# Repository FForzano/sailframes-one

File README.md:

# XGSail

Open sailing analytics platform for race analysis, session replay, and fleet performance — self-hostable, hardware-agnostic, and built for extensibility.

> ☕ **[Support XGSail on Buy Me a Coffee](https://buymeacoffee.com/xgsail)** — funds
> go toward app development, publishing on the app stores (once funding allows), and
> scaling up servers as usage grows.

> **XGSail is a fork of SailFrames (originally released as "SailFrames One").**
> It keeps the original's Apache 2.0 license and general purpose — sailing
> session analytics — but is **not a drop-in copy**: the data model, API
> surface, and frontend have been substantially redesigned rather than
> incrementally patched (see "Structural differences from upstream" below).
> The name change reflects that divergence and matches the domain this fork
> is hosted under.

XGSail is a software-first evolution of the original SailFrames project. It focuses on the application layer: user management, authentication, roles, data ingestion, storage, analytics, and web-based workflows for sailors, coaches, and teams.

## What XGSail Is

XGSail is a platform for collecting, storing, and analyzing sailing session data.

It provides:

- Self-hosted deployment (Postgres + MinIO + backend + frontend + workers, one `docker compose up`)
- User authentication and role-based access (clubs, groups, boats, per-resource ownership)
- Database-backed storage for users, boats, clubs, groups, devices, sessions, races and regattas
- Session and race analysis workflows (legs, maneuvers, VMG, polar performance)
- Replay and coaching-oriented review tools (track playback, session photos)
- Hardware-agnostic ingestion through a defined protocol (`docs/device-protocol.md`) — devices claim themselves, then upload data with a per-device key
- Native iOS/Android app shells (Capacitor) around the same frontend, with self-hosted OTA JS-bundle updates (`docs/native-apps.md`, `docs/ota-updates.md`) — still frontend application + deployment configuration scope, not a hardware artifact

The goal is to provide an open platform for sailing analytics that can work with dedicated devices, custom integrations, or external data sources, without tying the application to one specific hardware stack.

## What XGSail Is Not

XGSail is **not** the hardware, firmware, or embedded edge stack from the original SailFrames repository.

Those components may integrate with XGSail through the device protocol, but this repository is focused on the software platform and its data contract.

### XGSail E1 (reference hardware)

[**xgsail-e1**](https://github.com/FForzano/xgsail-e1) is a companion
repository with the firmware and KiCad PCB design for **E1**, an
ESP32-based fleet tracker built as reference hardware for this
platform: GNSS + IMU + wind + pressure logging, an ESP-NOW peer mesh
for live fleet position sharing and on-course-side (OCS) race-start
detection, and uploads over the device protocol above — direct over
WiFi, or relayed over Bluetooth by the owner's phone when WiFi isn't
available. It's open hardware (Apache 2.0, same license as this repo)
and currently a build-it-yourself project rather than a sold product.
See that repository's `README.md` and `docs/hardware.md` for firmware,
schematics, and the BOM.

## Project Scope

This repository contains:

- Backend API (`backend/`)
- Frontend application (`frontend/`)
- Database models and Alembic migrations (`backend/db/`)
- Authentication and authorization (`backend/auth/`)
- Storage and ingestion services (`backend/storage/`, `backend/services/`)
- Processing workers (`workers/`)
- Standalone OTA update server for the native app (`ota-service/`)
- Protocol and integration documentation (`docs/`)
- Self-hosted deployment configuration (`deploy/`, `docker-compose.yml`)

## Architecture Direction

XGSail follows a software-platform approach:

1. Devices or external tools produce sailing data.
2. Data is uploaded using a stable ingestion contract.
3. The backend validates, stores, and processes session data.
4. The web application exposes analysis, replay, and management features.

This separation allows the platform to evolve independently from any one hardware implementation.

## Repository Status

XGSail is under active development. The core platform is implemented and usable end to end:

- Users, authentication, and scoped RBAC (superadmin / club admin / race officer) plus per-resource ownership for boats and groups
- Clubs, groups, boats, and devices, with a claim-flow device protocol for ingestion
- Session import and processing (legs, maneuvers, VMG, polar targets), crew tracking, and photo attachments
- Races, regattas, and race-day management, with a leaderboard
- Multi-language frontend (English/Italian) covering all of the above

Ongoing work is on usability and polish of the existing frontend, and rounding out edge cases in the ingestion and analysis pipeline — not on building the core feature set from scratch.

## Relationship to SailFrames Core

XGSail is derived from the broader SailFrames effort, but it intentionally narrows the scope to the software application layer.

Where the original project includes hardware, firmware, edge devices, and AWS-oriented infrastructure, XGSail aims to become a cleaner, self-hostable analytics platform with a stable integration surface for present and future devices.

### Structural differences from upstream

This is a fork in lineage and license, not a rebrand of the same codebase. Concretely:

- **Data model**: the users/auth/roles/clubs/groups/devices/sessions schema was redesigned from scratch, not incrementally extended from the original tables.
- **API surface**: routes, permission model, and ingestion contract were rebuilt around that new schema, including a hardware-agnostic device-claim + device-key ingestion flow (`docs/device-protocol.md`) replacing the original's device-specific upload path.
- **Frontend**: rebuilt on a simplified page structure and data-fetching approach rather than carried over as-is.
- **Scope boundary**: firmware, PCB design, and embedded-device internals are excluded entirely — they remain in the upstream hardware repository, not mirrored here even partially.

The redesign these docs specified is now implemented on `main`. The
retained docs are the source of truth going forward: `docs/device-protocol.md`
(the ingestion contract) and `docs/estimation-pipeline.md` (how raw
sensor/API data becomes legs/maneuvers/VMG/polar numbers).

## Principles

- **Open** — users can inspect, run, and extend the platform
- **Self-hostable** — no mandatory vendor lock-in
- **Hardware-agnostic** — devices integrate through protocols, not tight coupling
- **Maintainable** — clear boundaries between frontend, backend, storage, and processing
- **Extensible** — new integrations should not require rewriting the core platform

## Quick start (self-host)

Everything runs as containers. From the repo root:

```bash
docker compose up --build
```

Then open **http://localhost:8080**. That's the whole stack:

| Service | Port | What it is |
|---|---|---|
| `frontend` | 8080 | The SPA (nginx). Serves the app and proxies `/api` → backend, so it's all one origin. |
| `backend` | 8000 | The REST API (FastAPI). Also reachable directly for debugging. |
| `postgres` | 5432 | Metadata (users, boats, sessions, races, RBAC). |
| `minio` | 9000 / 9001 | S3-compatible blob storage (sensor data, video, manifests) + console. |
| `process_upload`, `video` | — | Heavy-processing workers (see below). |

No `.env` is required — every value has a dev default. Copy `.env.example` to
`.env` to override secrets for a real deployment.

## Architecture

- **One API.** The FastAPI `backend/` is the only API surface. Metadata lives in
  Postgres; large files (CSV sensor data, video, JSON results) live in S3/MinIO.
- **Auth.** Email/password (Argon2id) → short-lived JWT access token + rotating
  refresh token, per-club RBAC. Dual transport: **web** uses httpOnly cookies with
  double-submit CSRF on mutations; **native apps** get the same tokens in the
  response body and send the access token as an `Authorization: Bearer` header
  (no cookie, so CSRF doesn't apply).
- **Workers as microservices.** `workers/process_upload` (GPS tracks + analysis)
  and `workers/video` (MP4 → HLS via ffmpeg) are built on the AWS Lambda base
  image. The **same image** runs on AWS Lambda and locally: in compose it runs
  via the Lambda Runtime Interface Emulator that ships in the base image, and the
  backend invokes it over HTTP on a MinIO upload event (`/hooks/minio`). On AWS
  the identical image sits behind an S3 → Lambda trigger. No code changes to move
  between the two.

Repo layout: `backend/` · `frontend/` · `workers/{process_upload,train_maneuver,video}/` ·
`ota-service/` (standalone OTA update server) · `deploy/` (Dockerfile + MinIO init) ·
`scripts/` (migrations, backfills, calibration) · `docs/device-protocol.md`
(device integration contract) · `docs/estimation-pipeline.md` (analysis pipeline).

## Native apps (iOS/Android)

The same frontend also ships as native iOS/Android shells via
[Capacitor](https://capacitorjs.com/) — not a separate codebase, just the
existing SPA wrapped for things a browser tab can't do (background GPS
recording, Bluetooth device pairing, share-target GPX import). See
`docs/native-apps.md` for how it's built and `docs/ota-updates.md` for how
JS/CSS updates reach installs without a store release.

**Status: early, not on the official stores.**

- **Android**: buildable and signable, but not published to the Play
  Store. `.github/workflows/android-release.yml` builds a signed release
  APK on every `vX.Y.Z` tag and attaches it to the matching GitHub
  Release — install it by sideloading that APK. A `play-store-upload` job
  exists in the same workflow but is disabled.
- **iOS**: not distributable in any form yet, not even for internal
  testing — `.github/workflows/ios-release.yml` is a scaffold, disabled.

**Why not on the stores yet: cost, not effort.** Google Play requires a
one-time $25 registration fee; Apple requires a $99/year Developer
Program membership just to sign a build at all, store or not (see
"Testing without a paid Apple account" in `docs/native-apps.md`). The
plan is to cover these through donations and publish once that's funded
— sideloading the GitHub Release APK is the path for Android in the
meantime, and iOS has no equivalent until an Apple account is in place.

## License

Apache 2.0, consistent with the original upstream project unless stated otherwise.

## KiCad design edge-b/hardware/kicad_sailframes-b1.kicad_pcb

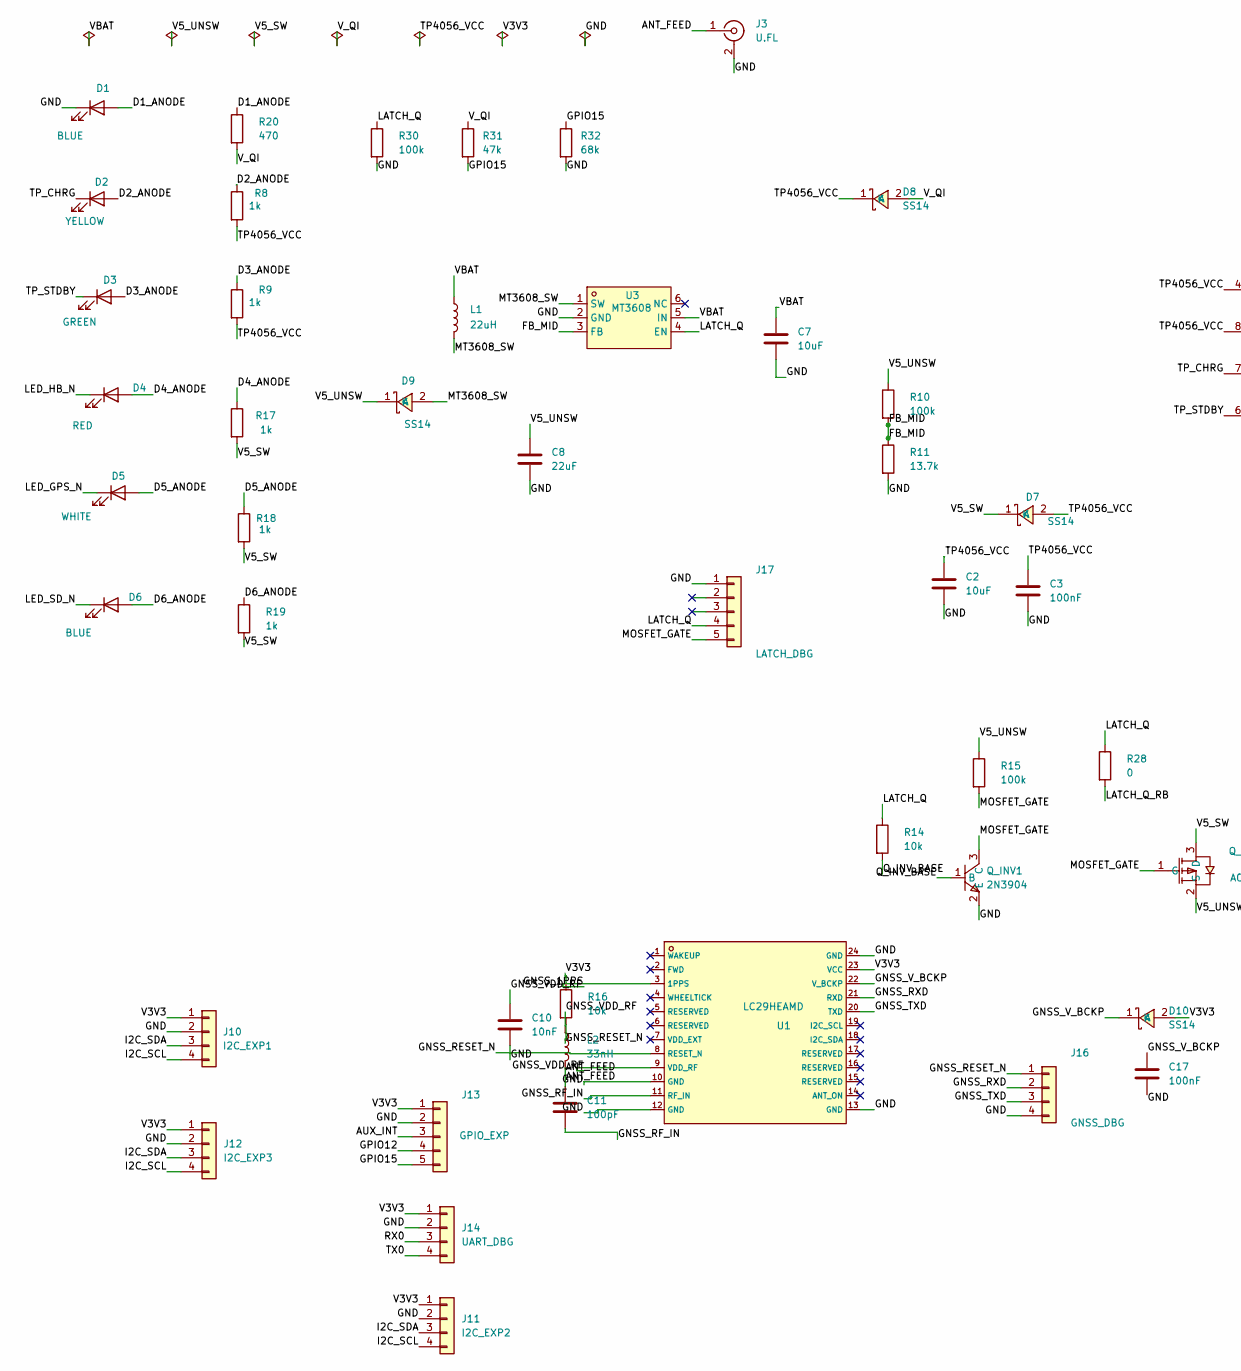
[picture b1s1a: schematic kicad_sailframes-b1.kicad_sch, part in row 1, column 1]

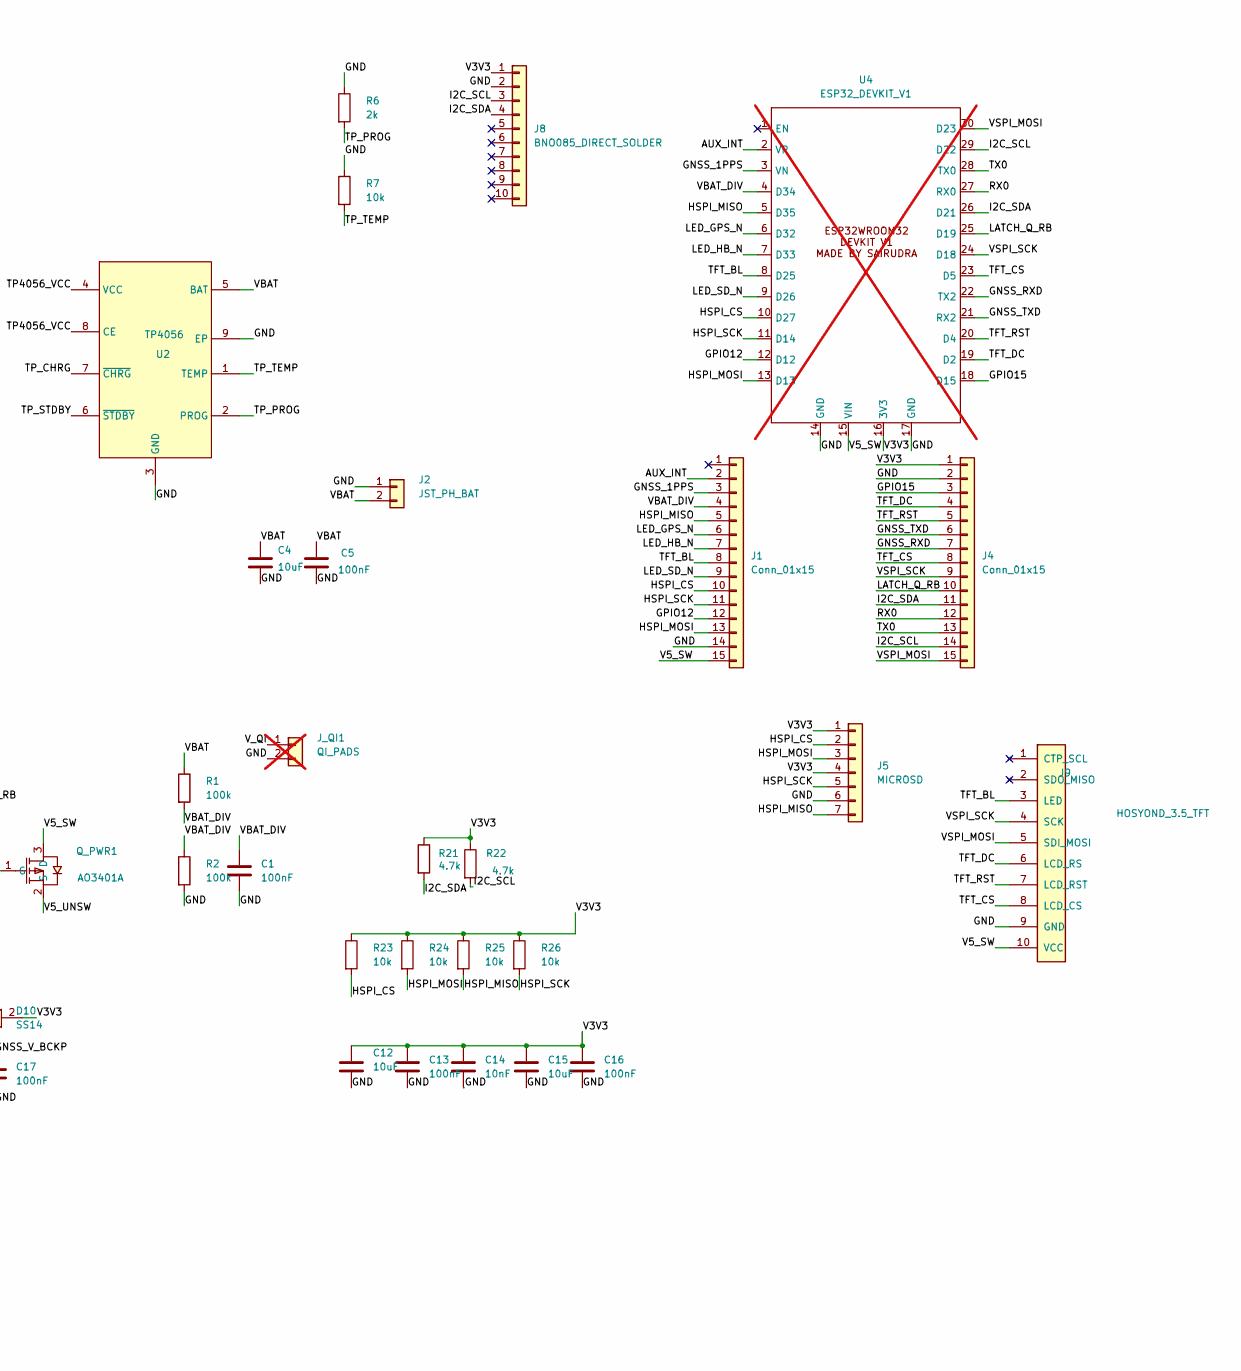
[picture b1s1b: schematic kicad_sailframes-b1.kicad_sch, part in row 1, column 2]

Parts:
C1, C3, C5, C13, C16, C17: 100nF; C_0603_1608Metric; LCSC Part # C14663
C2, C4, C7, C12, C15: 10uF; C_0603_1608Metric; LCSC Part # C19702
C8: 22uF; C_0603_1608Metric; LCSC Part # C59461
C10: 10nF; C_0402_1005Metric; LCSC Part # C15195
C11: 100pF; C_0402_1005Metric; LCSC Part # C1546
C14: 10nF; C_0603_1608Metric; LCSC Part # C57112
D1, D6: BLUE; LED_0603_1608Metric; LCSC Part # C99290
D2: YELLOW; LED_0603_1608Metric; LCSC Part # C89811
D3: GREEN; LED_0603_1608Metric; LCSC Part # C99289
D4: RED; LED_0603_1608Metric; LCSC Part # C2286
D5: WHITE; LED_0603_1608Metric; LCSC Part # C2290
D7, D8, D9, D10: SS14; D_SMA; LCSC Part # C2480
J1, J4: Conn_01x15; PinSocket_1x15_P2.54mm_Vertical; LCSC Part # C2932676
J2: JST_PH_BAT; JST_PH_S2B-PH-K_1x02_P2.00mm_Horizontal; LCSC Part # C173752
J3: U.FL; U.FL_Hirose_U.FL-R-SMT-1_Vertical; LCSC Part # C88374
J5: MICROSD; microSD_HC_Hirose_DM3D-SF; LCSC Part # C719027
J8: BNO085_DIRECT_SOLDER; PinHeader_1x10_P2.54mm_Vertical; LCSC Part # C57369
J9: HOSYOND_3.5_TFT; PinHeader_1x10_P2.54mm_Vertical; LCSC Part # C57369
J10: I2C_EXP1; PinHeader_1x04_P2.54mm_Vertical; LCSC Part # C5116483
J11: I2C_EXP2; PinHeader_1x04_P2.54mm_Vertical; LCSC Part # C5116483
J12: I2C_EXP3; PinHeader_1x04_P2.54mm_Vertical; LCSC Part # C5116483
J13: GPIO_EXP; PinHeader_1x05_P2.54mm_Vertical; LCSC Part # C5156614
J14: UART_DBG; PinHeader_1x04_P2.54mm_Vertical; LCSC Part # C5116483
J16: GNSS_DBG; PinHeader_1x04_P2.54mm_Vertical; LCSC Part # C5116483
J17: LATCH_DBG; PinHeader_1x05_P2.54mm_Vertical; LCSC Part # C5156614
J_QI1: QI_PADS; SolderWire-0.5sqmm_1x02_P4.6mm_D0.9mm_OD2.1mm_Relief; not fitted
L1: 22uH; L_Bourns_SRN6045TA; LCSC Part # C2044314
L2: 33nH; L_0402_1005Metric; LCSC Part # C32837
Q_INV1: 2N3904; SOT-23; LCSC Part # C20526
Q_PWR1: AO3401A; SOT-23; LCSC Part # C15127
R1, R2, R10, R15, R30: 100k; R_0603_1608Metric; LCSC Part # C25803
R6: 2k; R_0603_1608Metric; LCSC Part # C22975
R7, R14, R16, R23, R24, R25, R26: 10k; R_0603_1608Metric; LCSC Part # C25804
R8, R9, R17, R18, R19: 1k; R_0603_1608Metric; LCSC Part # C21190
R11: 13.7k; R_0603_1608Metric; LCSC Part # C22793
R20: 470; R_0603_1608Metric; LCSC Part # C23179
R21, R22: 4.7k; R_0603_1608Metric; LCSC Part # C23162
R28: 0; R_0603_1608Metric; LCSC Part # C17168
R31: 47k; R_0603_1608Metric; LCSC Part # C25819
R32: 68k; R_0603_1608Metric; LCSC Part # C23231
U1: LC29HEAMD; GPSM-SMD_24P-L16.0-W12.2-P1.10-TL; LCSC Part # C28453488
U2: TP4056; SOIC-8-1EP_3.9x4.9mm_P1.27mm_EP2.29x3mm_ThermalVias; LCSC Part # C16581
U3: MT3608; SOT-23-6; LCSC Part # C84817
U4: ESP32_DEVKIT_V1; ESP32DEVIKITV1; not fitted

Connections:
/ANT_FEED: C11.1, J3.1 (In), L2.2
/AUX_INT: J1.2, J13.3, U4.2 (VP)
/D1_ANODE: D1.2 (A), R20.1
/D2_ANODE: D2.2 (A), R8.1
/D3_ANODE: D3.2 (A), R9.1
/D4_ANODE: D4.2 (A), R17.1
/D5_ANODE: D5.2 (A), R18.1
/D6_ANODE: D6.2 (A), R19.1
/FB_MID: R10.2, R11.1, U3.3 (FB)
/GND: C1.2, C2.2, C3.2, C4.2, C5.2, C7.2, C8.2, C10.2, C12.2, C13.2, C14.2, C15.2, C16.2, C17.2, D1.1 (K), J1.14, J2.1, J3.2 (Ext), J4.2, J5.6, J8.2, J9.9 (GND), J10.2, J11.2, J12.2, J13.2, J14.2, J16.4, J17.1, J_QI1.2, Q_INV1.2 (E), R2.2, R6.1, R7.1, R11.2, R30.2, R32.2, U1.10 (GND), U1.12 (GND), U1.13 (GND), U1.24 (GND), U2.3 (GND), U2.9 (EP), U3.2 (GND), U4.14 (GND), U4.17 (GND)
/GNSS_1PPS: J1.3, U1.3 (1PPS), U4.3 (VN)
/GNSS_RESET_N: J16.1, R16.2, U1.8 (RESET_N)
/GNSS_RF_IN: C11.2, U1.11 (RF_IN)
/GNSS_RXD: J4.7, J16.2, U1.21 (RXD), U4.22 (TX2)
/GNSS_TXD: J4.6, J16.3, U1.20 (TXD), U4.21 (RX2)
/GNSS_VDD_RF: C10.1, L2.1, U1.9 (VDD_RF)
/GNSS_V_BCKP: C17.1, D10.1 (K), U1.22 (V_BCKP)
/GPIO12: J1.12, J13.4, U4.12 (D12)
/GPIO15: J4.3, J13.5, R31.2, R32.1, U4.18 (D15)
/HSPI_CS: J1.10, J5.2, R23.2, U4.10 (D27)
/HSPI_MISO: J1.5, J5.7, R25.2, U4.5 (D35)
/HSPI_MOSI: J1.13, J5.3, R24.2, U4.13 (D13)
/HSPI_SCK: J1.11, J5.5, R26.2, U4.11 (D14)
/I2C_SCL: J4.14, J8.3, J10.4, J11.4, J12.4, R22.2, U4.29 (D22)
/I2C_SDA: J4.11, J8.4, J10.3, J11.3, J12.3, R21.2, U4.26 (D21)
/LATCH_Q: J17.4, R14.1, R28.1, R30.1, U3.4 (EN)
/LATCH_Q_RB: J4.10, R28.2, U4.25 (D19)
/LED_GPS_N: D5.1 (K), J1.6, U4.6 (D32)
/LED_HB_N: D4.1 (K), J1.7, U4.7 (D33)
/LED_SD_N: D6.1 (K), J1.9, U4.9 (D26)
/MOSFET_GATE: J17.5, Q_INV1.3 (C), Q_PWR1.1 (G), R15.2
/MT3608_SW: D9.2 (A), L1.2, U3.1 (SW)
/Q_INV_BASE: Q_INV1.1 (B), R14.2
/RX0: J4.12, J14.3, U4.27 (RX0)
/TFT_BL: J1.8, J9.3 (LED), U4.8 (D25)
/TFT_CS: J4.8, J9.8 (LCD_CS), U4.23 (D5)
/TFT_DC: J4.4, J9.6 (LCD_RS), U4.19 (D2)
/TFT_RST: J4.5, J9.7 (LCD_RST), U4.20 (D4)
/TP4056_VCC: C2.1, C3.1, D7.2 (A), D8.1 (K), R8.2, R9.2, U2.4 (VCC), U2.8 (CE)
/TP_CHRG: D2.1 (K), U2.7 (~CHRG)
/TP_PROG: R6.2, U2.2 (PROG)
/TP_STDBY: D3.1 (K), U2.6 (~STDBY)
/TP_TEMP: R7.2, U2.1 (TEMP)
/TX0: J4.13, J14.4, U4.28 (TX0)
/V3V3: C12.1, C13.1, C14.1, C15.1, C16.1, D10.2 (A), J4.1, J5.1, J5.4, J8.1, J10.1, J11.1, J12.1, J13.1, J14.1, R16.1, R21.1, R22.1, R23.1, R24.1, R25.1, R26.1, U1.23 (VCC), U4.16 (3V3)
/V5_SW: D7.1 (K), J1.15, J9.10 (VCC), Q_PWR1.3 (D), R17.2, R18.2, R19.2, U4.15 (VIN)
/V5_UNSW: C8.1, D9.1 (K), Q_PWR1.2 (S), R10.1, R15.1
/VBAT: C4.1, C5.1, C7.1, J2.2, L1.1, R1.1, U2.5 (BAT), U3.5 (IN)
/VBAT_DIV: C1.1, J1.4, R1.2, R2.1, U4.4 (D34)
/VSPI_MOSI: J4.15, J9.5 (SDI_MOSI), U4.30 (D23)
/VSPI_SCK: J4.9, J9.4 (SCK), U4.24 (D18)
/V_QI: D8.2 (A), J_QI1.1, R20.2, R31.1

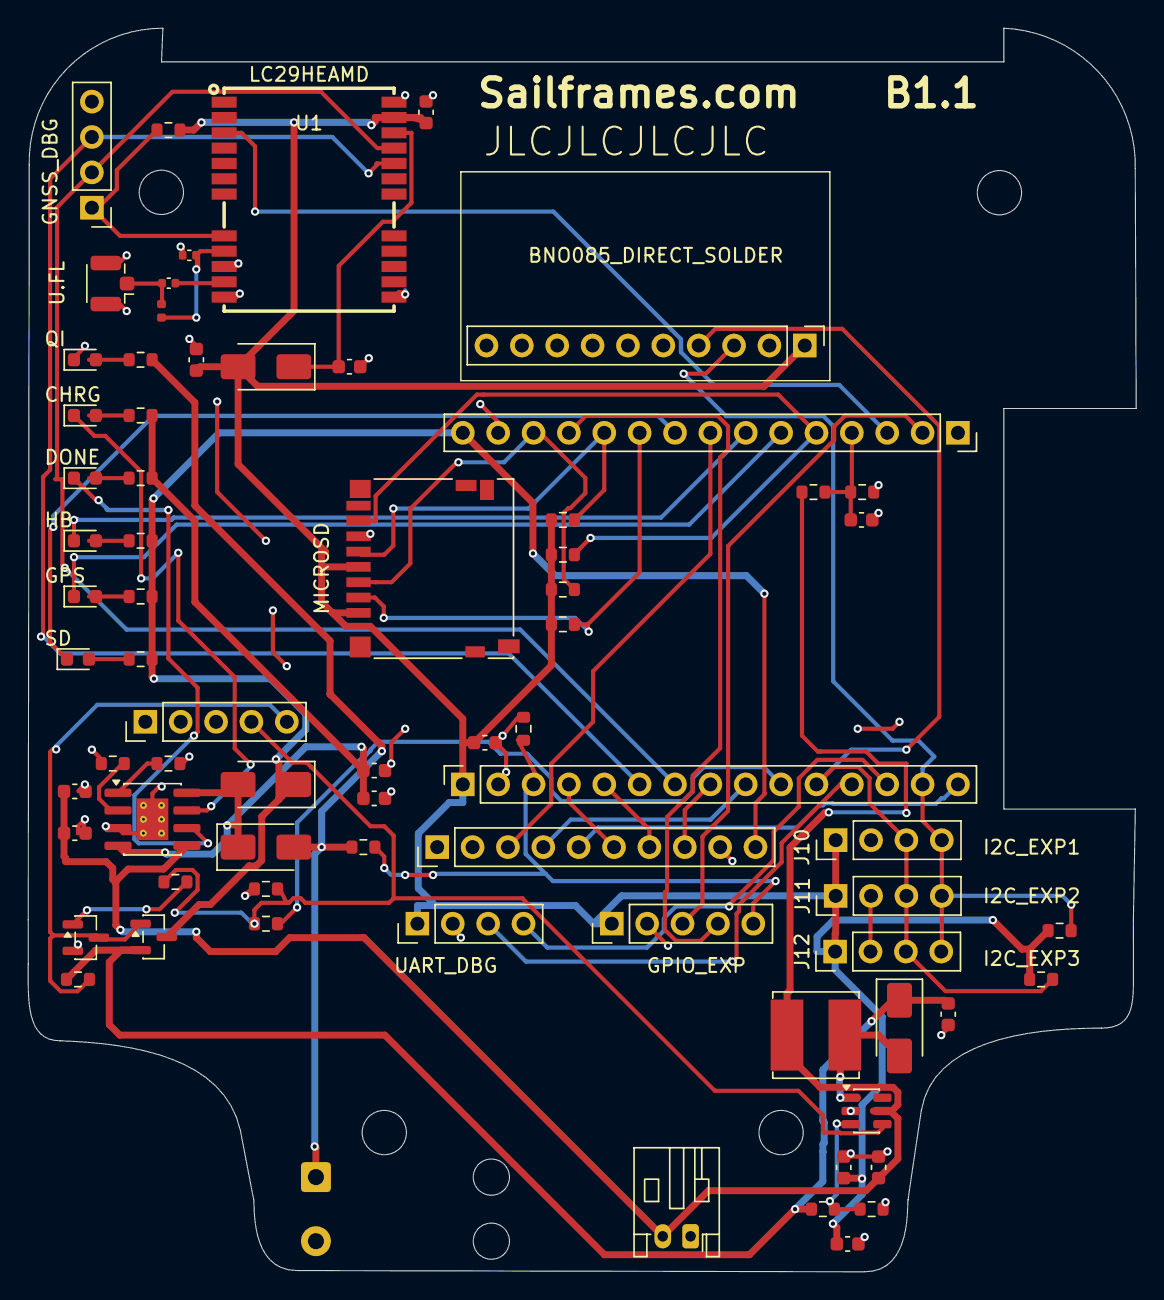
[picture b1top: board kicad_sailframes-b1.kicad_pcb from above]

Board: 2 copper layers, 79.6 x 89.3 mm, 72 parts (1 on the bottom side), 52 nets.

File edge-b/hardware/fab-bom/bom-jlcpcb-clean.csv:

Comment,Designator,Footprint,JLCPCB Part #
10nF,C14,C_0603_1608Metric,C57112
2N3904,Q_INV1,SOT-23,C20526
MT3608,U3,SOT-23-6,C84817
LATCH_DBG,"J13,J17",PinHeader_1x05_P2.54mm_Vertical,C5156614
U.FL,J3,U.FL_Hirose_U.FL-R-SMT-1_Vertical,C88374
100nF,"C1,C3,C5,C9,C13,C16,C17",C_0603_1608Metric,C14663
13.7k,R11,R_0603_1608Metric,C22793
Conn_01x15,"J1,J4",PinSocket_1x15_P2.54mm_Vertical,C2932676
SN74LVC1G74,U_FF1,VSSOP-8_DCU_2.3x2mm_P0.65mm,C70285
RED,D4,LED_0603_1608Metric,C2286
HOSYOND_3.5_TFT,"J8,J9",PinHeader_1x10_P2.54mm_Vertical,C57369
BAT54,D11,D_SOD-323,C7502694
AO3401A,Q_PWR1,SOT-23,C15127
WHITE,D5,LED_0603_1608Metric,C2290
LC29HEAMD,U1,GPSM-SMD_24P-L16.0-W12.2-P1.10-TL,C28453488
JST_PH_BAT,J2,JST_PH_S2B-PH-K_1x02_P2.00mm_Horizontal,C173752
10uF,"C2,C4,C7,C12,C15",C_0603_1608Metric,C19702
2k,R6,R_0603_1608Metric,C22975
I2C_EXP2,"J10,J11,J12,J14,J16",PinHeader_1x04_P2.54mm_Vertical,C5116483
22uH,L1,L_Bourns_SRN6045TA,C2044314
J_AUX,J15,PinHeader_1x06_P2.54mm_Vertical,C32713272
33nH,L2,L_0402_1005Metric,C32837
MAX809T,U_RST1,SOT-23,C347372
SS14,"D7,D8,D9,D10",D_SMA,C2480
100pF,C11,C_0402_1005Metric,C1546
GREEN,D3,LED_0603_1608Metric,C99289
TP4056,U2,SOIC-8-1EP_3.9x4.9mm_P1.27mm_EP2.29x3mm_ThermalVias,C16581
BLUE,"D1,D6",LED_0603_1608Metric,C99290
22uF,C8,C_0603_1608Metric,C59461
MICROSD,J5,microSD_HC_Hirose_DM3D-SF,C719027
10nF,C10,C_0402_1005Metric,C15195
4.7k,"R21,R22",R_0603_1608Metric,C23162
10k,"R7,R13,R14,R16,R23,R24,R25,R26,R27,R28",R_0603_1608Metric,C25804
DRV5032AJDBZR,U_HALL1,SOT-23,C266120
1k,"R8,R9,R17,R18,R19",R_0603_1608Metric,C21190
100k,"R1,R2,R10,R12,R15",R_0603_1608Metric,C25803
470,R20,R_0603_1608Metric,C23179
YELLOW,D2,LED_0603_1608Metric,C89811

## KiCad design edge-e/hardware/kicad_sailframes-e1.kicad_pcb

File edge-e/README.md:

# SailFrames Edge-E

ESP32-based edge device for sailboat racing data acquisition.

Part of [sailframes/core](https://github.com/sailframes/core). See [edge-s](../edge-s) for Raspberry Pi-based device.

## Variants

- **E1** - First generation ESP32 device (current)

## Hardware (E1)

| Component | Part | Interface |
|-----------|------|-----------|
| MCU | ESP32 | — |
| GPS | u-blox | UART |
| IMU | ICM-20948 or BNO085 | I2C |
| Storage | MicroSD | SPI |

## Directory Structure

```
edge-e/
├── hardware/          # KiCad PCB designs
│   ├── *.kicad_sch    # Schematic
│   ├── *.kicad_pcb    # PCB layout
│   └── *.kicad_pro    # Project file
└── firmware/          # ESP32/Arduino firmware
    └── sailframes_edge/ # unified edge firmware (E + B devices)
```

## KiCad

Open the project in KiCad 8+:

```bash
cd edge-e/hardware
kicad kicad_sailframes-e1.kicad_pro
```

## Firmware

Build and flash using Arduino IDE or PlatformIO:

```bash
cd edge-e/firmware/sailframes_edge
# Open in Arduino IDE or use PlatformIO
```

## Edge-S vs Edge-E

| Feature | Edge-S (Pi) | Edge-E (ESP32) |
|---------|-------------|----------------|
| Camera | Yes (Pi Camera 3) | No |
| Video recording | Yes | No |
| Dashboard | Yes (web server) | No |
| Power consumption | ~5-7W | <1W |
| Cost | Higher | Lower |
| Use case | Full data + video | Lightweight logging |

## License

Apache 2.0

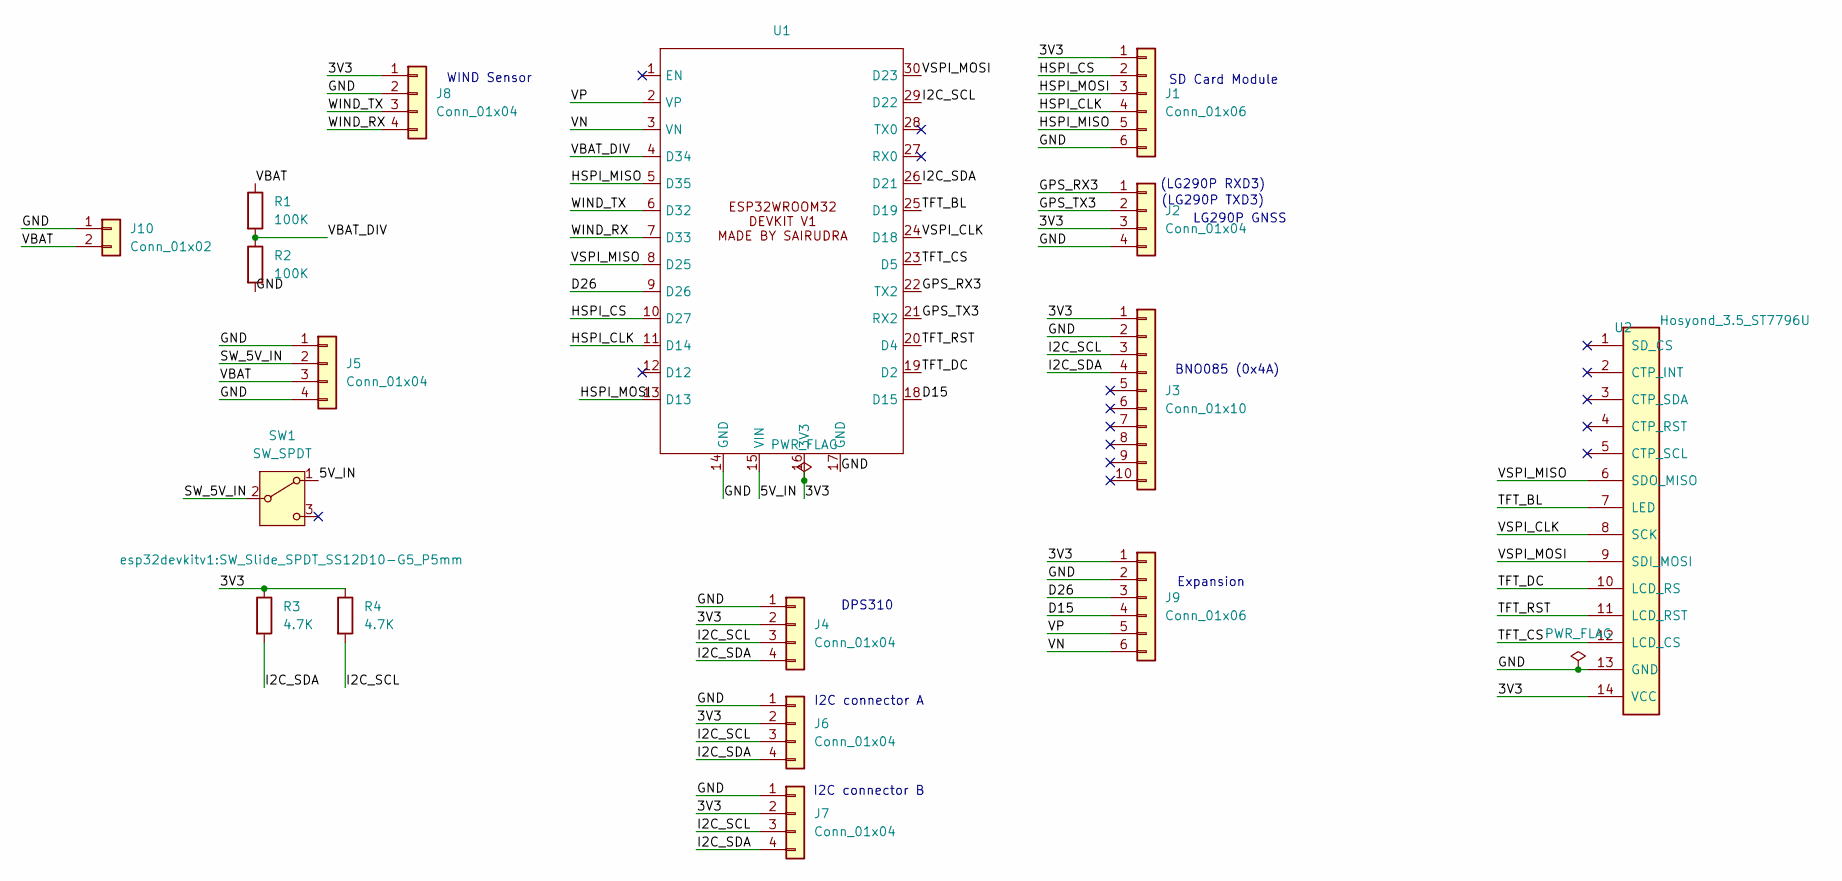
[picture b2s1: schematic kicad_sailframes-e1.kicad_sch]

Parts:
J1: Conn_01x06; SD_CARD
J2, J4, J5, J6, J7, J8: Conn_01x04; PinHeader_1x04_P2.54mm_Vertical
J3: Conn_01x10; PinHeader_1x10_P2.54mm_Vertical
J9: Conn_01x06; PinHeader_1x06_P2.54mm_Vertical
J10: Conn_01x02; JST_PH_S2B-PH-K_1x02_P2.00mm_Horizontal
R1, R2: 100K; R_0805_2012Metric
R3, R4: 4.7K; R_0805_2012Metric
SW1: SW_SPDT; SW_Slide_SPDT_SS12D10-G5_P5mm
U1: ESP32DEVIKITV1
U2: Hosyond_3.5_ST7796U; PinHeader_1x14_P2.54mm_Vertical

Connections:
/3V3: J1.1, J2.3, J3.1, J4.2, J6.2, J7.2, J8.1, J9.1, R3.1, R4.1, U1.16 (3V3), U2.14 (VCC)
/5V_IN: SW1.1 (A), U1.15 (VIN)
/D15: J9.4, U1.18 (D15)
/D26: J9.3, U1.9 (D26)
/GND: J1.6, J2.4, J3.2, J4.1, J5.1, J5.4, J6.1, J7.1, J8.2, J9.2, J10.1, R2.2, U1.14 (GND), U1.17 (GND), U2.13 (GND)
/GPS_RX3: J2.1, U1.22 (TX2)
/GPS_TX3: J2.2, U1.21 (RX2)
/HSPI_CLK: J1.4, U1.11 (D14)
/HSPI_CS: J1.2, U1.10 (D27)
/HSPI_MISO: J1.5, U1.5 (D35)
/HSPI_MOSI: J1.3, U1.13 (D13)
/I2C_SCL: J3.3, J4.3, J6.3, J7.3, R4.2, U1.29 (D22)
/I2C_SDA: J3.4, J4.4, J6.4, J7.4, R3.2, U1.26 (D21)
/SW_5V_IN: J5.2, SW1.2 (B)
/TFT_BL: U1.25 (D19), U2.7 (LED)
/TFT_CS: U1.23 (D5), U2.12 (LCD_CS)
/TFT_DC: U1.19 (D2), U2.10 (LCD_RS)
/TFT_RST: U1.20 (D4), U2.11 (LCD_RST)
/VBAT: J5.3, J10.2, R1.1
/VBAT_DIV: R1.2, R2.1, U1.4 (D34)
/VN: J9.6, U1.3 (VN)
/VP: J9.5, U1.2 (VP)
/VSPI_CLK: U1.24 (D18), U2.8 (SCK)
/VSPI_MISO: U1.8 (D25), U2.6 (SDO_MISO)
/VSPI_MOSI: U1.30 (D23), U2.9 (SDI_MOSI)
/WIND_RX: J8.4, U1.7 (D33)
/WIND_TX: J8.3, U1.6 (D32)

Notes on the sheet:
Expansion
LG290P GNSS
(LG290P RXD3)
(LG290P TXD3)
SD Card Module
BNO085 (0x4A)
WIND Sensor
I2C connector A
DPS310
I2C connector B

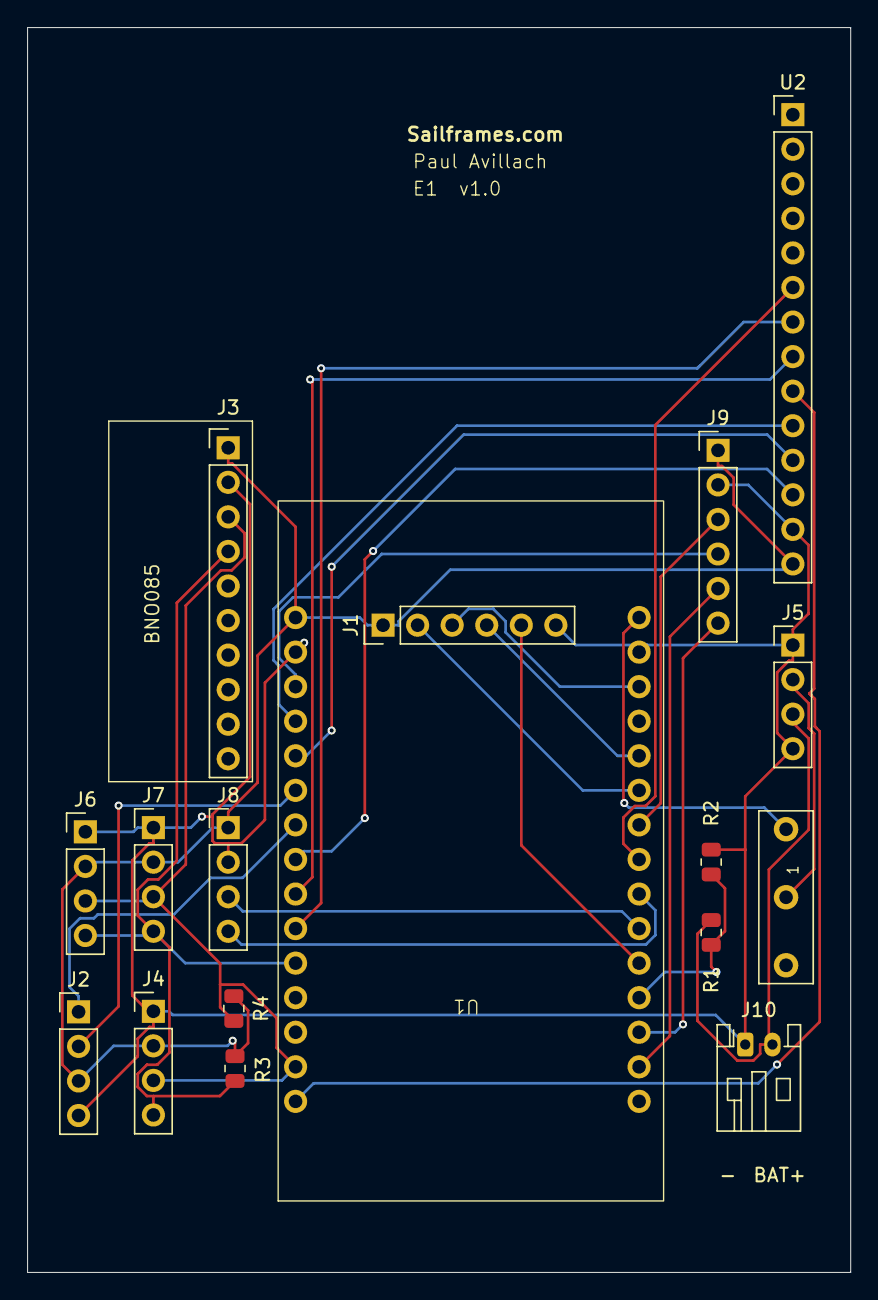
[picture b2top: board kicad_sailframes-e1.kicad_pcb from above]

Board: 2 copper layers, 60.5 x 91.5 mm, 17 parts (0 on the bottom side), 27 nets.

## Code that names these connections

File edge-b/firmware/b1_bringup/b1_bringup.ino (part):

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#define GNSS_PPS   39     // input-only
// Battery + power latch
#define PIN_VBAT   34     // ADC1_6, 100K/100K divider on VBAT
#define PIN_LATCH  19     // LATCH_Q_RB (read-only — latch set => board ON)
// Status LEDs (active LOW, 220R)
#define LED_RED    33     // D4
#define LED_WHITE  32     // D5
#define LED_CYAN   26     // D6
// TFT backlight (B1 = GPIO25)
#define TFT_BL     25

SPIClass sdSPI(HSPI);
bool g_sdOK = false;
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static void testLatch() {
  pinMode(PIN_LATCH, INPUT);
  int q = digitalRead(PIN_LATCH);
  Serial.printf("[LATCH] LATCH_Q_RB (GPIO19) = %d  -> latch %s (we're running, so should read HIGH)\n",
                q, q ? "SET / board ON" : "CLEAR (?)");
}

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    Serial.printf("[GNSS] @%lu: %d bytes, NMEA %s\n", (unsigned long)bauds[b], bytes, nmea ? "SEEN -> alive" : "none");
    if (bytes) return;   // got data at this baud; stop
  }
  Serial.println(F("[GNSS] no bytes at either baud — check LC29HEA power(V3V3), TXD1->GPIO16 wiring, D_SEL pulls"));
}

// ---------------- TFT ----------------
#if TEST_TFT
static void testTFT() {
  pinMode(TFT_BL, OUTPUT); digitalWrite(TFT_BL, HIGH);   // backlight full on
  tft.init();
  tft.setRotation(0);
  tft.fillScreen(TFT_BLACK);
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
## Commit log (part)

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2026-04-07 Fix TWS/TWA formulas: wrong signs caused incorrect wind calculations
    TWS formula had + instead of - (2·AWS·SOG·cos(AWA) term).
    TWA formula had + SOG instead of - SOG, producing ~329° instead
    of the correct angle. Comments showed the right formulas but
    code implemented them with inverted signs.
    Also added wind_offset config parameter (degrees) for sensor
    mounting calibration — set in config.txt if Calypso bow mark
2026-04-09 E1: keep IMU/pressure sensors running during WiFi upload
    Upload now runs entirely on Core 0, sensor reads are I2C on Core 1 — no
    conflict. SD logging is already guarded by the `logging` flag which is
    always false during upload. No reason to blank out heel/pitch/pressure
    on the display while uploading.
    https://claude.ai/code/session_019i1uJZTk7fZJ9ZwSkWvr92
2026-04-09 E1: stop deiniting BLE during WiFi upload — no longer needed
    BLE deinit was required when uploads used TLS (mbedTLS needed ~50KB heap,
    BLE competed for memory). Uploads now use plain HTTP to S3 — no TLS memory
    pressure. ESP32 can time-slice WiFi and BLE on the shared radio for basic
    HTTP PUTs. Wind sensor stays connected during uploads.
    https://claude.ai/code/session_019i1uJZTk7fZJ9ZwSkWvr92
2026-04-20 Add race course editor with marks, start/finish lines, and auto-suggest
    - web/race.html: Edit Course button, toolbar (Start/Finish/+Mark/Auto
    Start/Auto Marks/Done/Cancel), mark list panel
    - web/assets/js/race-app.js: course editor mode with draggable Leaflet
    markers for line endpoints and marks, type/name editing, PATCH on save
    - web/assets/css/race.css: toolbar, mark list, and course marker styles
    - lambda/api_race/handler.py: persist marks/course in create/update, add
2026-04-20 Fix race timeline being covered by Leaflet map
    Add z-index: 1100 to .timeline-container so it sits above the Leaflet
    map layer (z-index 1000) instead of being hidden behind it.
2026-05-21 v2.0.0 Stage 1 foundation: HW platform / unit role / radio mode skeleton
    Stage 1 of SF_FIRMWARE_V2_SPEC.md — mechanism-only, no behavioral change vs .05.17.01 at default config.
    * FW_VERSION 2026.05.17.01 -> 2026.05.20.01
    * v2_types.h: HardwarePlatform / UnitRole / RadioMode enums (own header
    so the Arduino .ino preprocessor can't auto-generate stale prototypes)
    * Globals g_hw / g_role / g_radio_mode default HW_E1 / ROLE_RACING_BOAT
    / MODE_BOOT - preserves pre-2.0 behavior on existing fleet configs
2026-05-21 WiFi: pin association to strongest BSSID per configured SSID
    ESP32 Arduino Core 3.3.7 default WiFi.begin picks "first BSSID that
    auth-completes", not strongest. On multi-AP mesh that lets boats
    latch onto a far AP at -90 dBm even when same SSID is broadcast
    nearby at -45 dBm. Observed 2026-05-21 with E5 stuck on Wifi Family
    room (ch 1) at -90 dBm while Wifi Office (same room as boat, ch 6)
    was at -45 dBm — OTA throughput ~2.5 KB/s, 40% TX retries.
2026-05-21 Bake 10 Hz GNSS + 10 Hz IMU into firmware (drop config knobs)
    config.txt should hold per-boat / per-club state, not fleet-invariant
    sample rates. Drop the Stage 1 opt-in knobs and bake the rates in.
    * IMU_INTERVAL_MS 1000 -> 100 (10 Hz BNO085 reports)
    * configureLG290P unconditionally sends PQTMCFGFIXRATE,W,100 +
    PQTMSAVEPAR (persists to LG290P NVM)
    * Remove gps_rate_hz / imu_interval_ms / gps_set_fixrate from
2026-05-21 OTA screen: bump small labels to font 4, taller progress bar
    User feedback: OTA update screen is great, just make font bigger.
    The percentage (font 8) was fine; the smaller labels were not.
    * target version: font 2 -> font 4
    * phase ("downloading..." / "verifying..." / "rebooting..."): font 2 -> font 4
    * "DO NOT POWER OFF" footer: font 2 -> font 4
    * Progress bar: 30 px -> 40 px tall
2026-05-21 Retire PPK / raw-RTCM3; LG290P → Rover @ 10 Hz NMEA
    PPK was a strategic differentiator but LG290P forces a hard trade:
    MSM only in Base mode (1 Hz locked) vs 10 Hz only in Rover mode
    (where PQTMCFGRTCM silently emits zero MSM on firmware AANR01A06S
    despite the spec). E2+E4 22 min car ride on .07 produced 1.5 KB
    .rtcm3 each, zero MSM7 frames.
    10 Hz GNSS wins: OCS, tack analysis, and v2.0.0 race-features all
2026-05-21 Web + AWS: drop PPK UI, rebrand 1Hz→10Hz, disable MAMI CORS cron
    Aligns dashboard + AWS infrastructure with firmware .09 PPK retirement.
    session.html: collapse three track buttons -> one "GNSS 10Hz"
    Drop "PPK:" header stat
    map-view.js: drop ppkData/gps10HzData state, layers, methods,
    _handleTrack10HzClick, stat-ppk-quality lookup
    app.js: drop /api/data ?sensors=gps_10hz and ?sensors=ppk fetches,
2026-05-22 HOTFIX .12: comment out radioModeTransition() too — .11 may also panic
    Multiple boats (E2, E6) on .10 panic identically at setup() exit
    with Reset reason: PANIC (4). Subsequent boots fail SD init too —
    panic is leaving SD in a corrupted state, implicating the
    appendBootLog() SD-write path.
    appendBootLog is called from BOTH new-in-.10 setup calls:
    - meshInit() — disabled in .11
2026-05-22 v2.0.0 Stage 2 .13: fix single-byte stack overflow that bricked .10/.11
    Linker-map analysis revealed meshTick() was the real panicking
    function, not setup(). Inside meshBuildAndSendBoatState:
    p->reserved[0] = p->reserved[1] = p->reserved[2] = 0;
    reserved was sized [2] in mesh.h (struct sized to 20 bytes per spec).
    p->reserved[2] wrote ONE BYTE past the end of buf[36] on the stack.
    -fstack-protector caught it correctly every meshTick call.
2026-05-22 Stage 2 .14: force WiFi STA + pin channel — fix tx=0 fail=N on mesh
    .13 fleet: mesh enabled, no panic, but tx=0 fail=68 — every send
    fails. Root cause:
    - Early setup() WiFi.disconnect(true) calls esp_wifi_stop().
    Radio off. esp_now_init registers callbacks but the radio
    must be physically on for esp_now_send to transmit.
    - Broadcast peer registered with channel=0 ("current STA
2026-05-22 .15: clear wifiBusy after OTA-only check — unblocks meshTick + teardown
    Field on .14: 5 boats all frozen at tx=71 after their OTA-only check
    fired. Every boat's mesh stops broadcasting once it hits "Already
    up to date" — wifiBusy stuck true in the success branch.
    Single-line fix: clear wifiBusy after performOTAUpdate in the
    WiFi-connected branch. Teardown block can now proceed; meshTick
    resumes 2 Hz broadcasts.
2026-06-30 Enhance error handling for S3 client and add support for NoSuchBucket error
